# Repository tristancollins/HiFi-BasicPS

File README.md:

# A simple power supply board

This takes non-rectifed HT and converts to DC, with 2 or 3 stages of RC smoothing. Also, a footprint is there for a Tentlabs electronic choke (capacitor multiplier?).

It also takes AC heater feed and passes it to two take-off points. Or it rectifies it to DC.

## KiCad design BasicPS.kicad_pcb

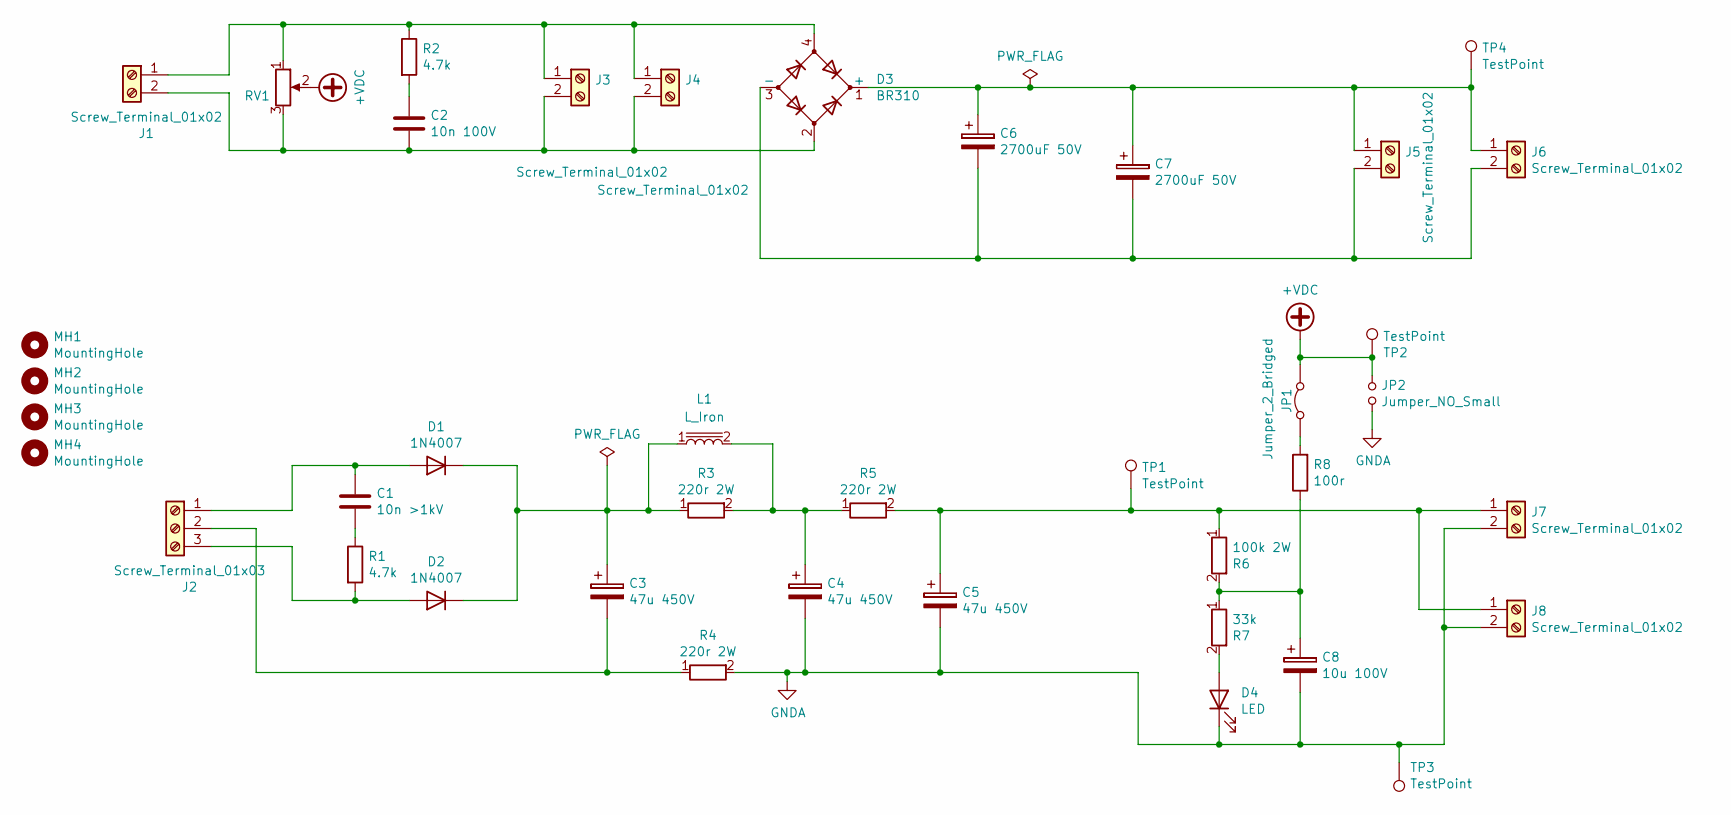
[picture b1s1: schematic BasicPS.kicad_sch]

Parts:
C1: 10n >1kV; C_Disc_D4.3mm_W1.9mm_P5.00mm
C2: 10n 100V; C_Disc_D4.3mm_W1.9mm_P5.00mm
C3, C4, C5: 47u 450V; CP_Radial_D16.0mm_P7.50mm
C6, C7: 2700uF 50V; CP_Radial_D22.0mm_P10.00mm_SnapIn
C8: 10u 100V; CP_Radial_D8.0mm_P5.00mm
D1, D2: 1N4007; D_DO-41_SOD81_P10.16mm_Horizontal
D3: BR310; Diode_Bridge_16.7x16.7x6.3mm_P10.8mm
D4: LED; LED_D3.0mm
J1, J3, J4, J5, J6, J7, J8: Screw_Terminal_01x02; PhoenixContact_MCV_1,5_2-G-5.08_1x02_P5.08mm_Vertical
J2: Screw_Terminal_01x03; PhoenixContact_MCV_1,5_3-G-5.08_1x03_P5.08mm_Vertical
JP1: Jumper_2_Bridged; SolderJumper-2_P1.3mm_Bridged_RoundedPad1.0x1.5mm
JP2: Jumper_NO_Small; SolderJumper-2_P1.3mm_Open_RoundedPad1.0x1.5mm
L1: L_Iron; TentChoke
MH1, MH2, MH3, MH4: MountingHole; MountingHole_3.2mm_M3
R1, R2: 4.7k; R_Axial_DIN0207_L6.3mm_D2.5mm_P10.16mm_Horizontal
R3, R4, R5: 220r 2W; R_Axial_DIN0414_L11.9mm_D4.5mm_P20.32mm_Horizontal
R6: 100k 2W; R_Axial_DIN0414_L11.9mm_D4.5mm_P20.32mm_Horizontal
R7: 33k; R_Axial_DIN0207_L6.3mm_D2.5mm_P10.16mm_Horizontal
R8: 100r; R_Axial_DIN0207_L6.3mm_D2.5mm_P10.16mm_Horizontal
RV1: 500r; Potentiometer_Bourns_3339P_Vertical
TP1, TP2, TP3, TP4: TestPoint; TestPoint_Keystone_5005-5009_Compact

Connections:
+VDC: JP1.2 (B), JP2.1, RV1.2, TP2.1
GNDA: C4.2, C5.2, C8.2, D4.1 (K), J7.2, J8.2, JP2.2, R4.2, TP3.1
unnamed: C1.2, R1.1
unnamed: C2.1, R2.2
unnamed: C4.1, L1.2, R3.2, R5.1
unnamed: C8.1, R6.2, R7.1, R8.1
unnamed: C1.1, D1.2 (A), J2.1
unnamed: C3.1, D1.1 (K), D2.1 (K), L1.1, R3.1
unnamed: D2.2 (A), J2.3, R1.2
unnamed: C6.1, C7.1, D3.1 (+), J5.1, J6.1, TP4.1
unnamed: C6.2, C7.2, D3.3 (-), J5.2, J6.2
unnamed: D4.2 (A), R7.2
unnamed: D3.4, J1.1, J3.1, J4.1, R2.1, RV1.1
unnamed: C2.2, D3.2, J1.2, J3.2, J4.2, RV1.3
unnamed: C3.2, J2.2, R4.1
unnamed: C5.1, J7.1, J8.1, R5.2, R6.1, TP1.1
unnamed: JP1.1 (A), R8.2

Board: 2 copper layers, 40 parts (2 on the bottom side), 17 nets, no tracks yet.

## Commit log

2024-07-29 some tidy up
2024-07-29 more layout playing
2024-08-01 further clean-up and additions
2024-08-08 more tidy up, change grounding
2024-08-13 adding choke
2024-08-13 rename project
2024-08-13 remove legacy files
2024-08-13 tidy up
2024-08-19 adding readme
2024-08-19 rename readme
